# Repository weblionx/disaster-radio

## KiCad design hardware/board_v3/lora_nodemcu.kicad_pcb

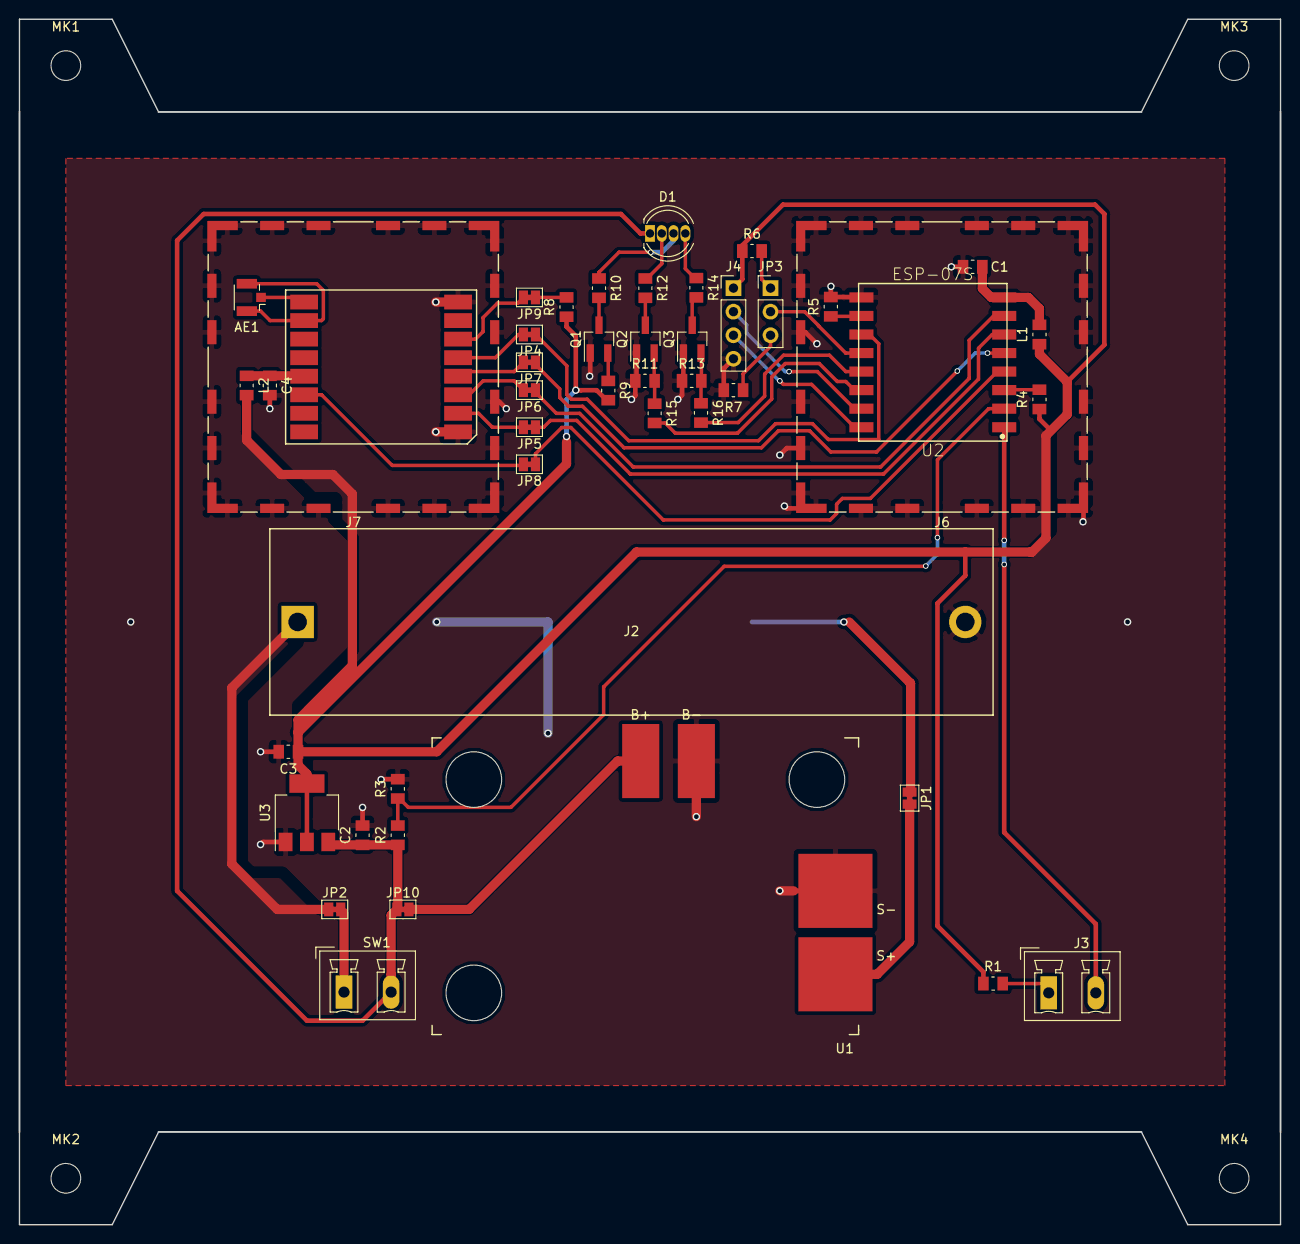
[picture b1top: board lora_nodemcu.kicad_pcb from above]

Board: 2 copper layers, 136.0 x 130.0 mm, 52 parts (1 on the bottom side), 45 nets.

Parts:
AE1: RFM95_Antenna; U.FL_Hirose_U.FL-R-SMT-1_Vertical
C1, C4: 0.1uF; C_0805_2012Metric_Pad1.15x1.50mm_HandSolder
C2, C3: 10uF; C_0805_2012Metric_Pad1.15x1.50mm_HandSolder
D1: LED_ARGB; LED_D5.0mm-4
J1: Solar Panel; solar_panel_conn
J2: LiPo 18650; BatteryHolder_MPD_BH-18650-PC2
J3: RESET_BUTTON; PhoenixContact_MCV_1,5_2-G-5.08_1x02_P5.08mm_Vertical
J4: ESP_PRGM; PinHeader_1x04_P2.54mm_Vertical
J6: RF_Shield_ESP-07S; Wuerth_36103305_30x30mm
J7: RF_Shield_RFM95; Wuerth_36103305_30x30mm
JP1: SOLAR_TP; SolderJumper-2_P1.3mm_Bridged_Pad1.0x1.5mm
JP2: LiPo_TP; SolderJumper-2_P1.3mm_Bridged_Pad1.0x1.5mm
JP3: PRGM_SELECT; PinHeader_1x03_P2.54mm_Vertical
JP4: CS; SolderJumper-2_P1.3mm_Bridged_Pad1.0x1.5mm
JP5: MISO; SolderJumper-2_P1.3mm_Bridged_Pad1.0x1.5mm
JP6: MOSI; SolderJumper-2_P1.3mm_Bridged_Pad1.0x1.5mm
JP7: CLK; SolderJumper-2_P1.3mm_Bridged_Pad1.0x1.5mm
JP8: D1; SolderJumper-2_P1.3mm_Bridged_Pad1.0x1.5mm
JP9: RST; SolderJumper-2_P1.3mm_Bridged_Pad1.0x1.5mm
JP10: MPPT_TP; SolderJumper-2_P1.3mm_Bridged_Pad1.0x1.5mm
L1, L2: JUMPER; L_0805_2012Metric_Pad1.15x1.50mm_HandSolder
MK1, MK2, MK3, MK4: Mounting_Hole; MountingHole_3.2mm_M3
Q1, Q2, Q3: 2N3904; SOT-23_Handsoldering
R1, R3, R4, R5, R6, R7, R8, R9, R11, R13, R15, R16: 10K; R_0805_2012Metric_Pad1.15x1.50mm_HandSolder
R2: 47K; R_0805_2012Metric_Pad1.15x1.50mm_HandSolder
R10: 1K; R_0805_2012Metric_Pad1.15x1.50mm_HandSolder
R12: 470; R_0805_2012Metric_Pad1.15x1.50mm_HandSolder
R14: 330; R_0805_2012Metric_Pad1.15x1.50mm_HandSolder
SW1: SW_SPST; PhoenixContact_MCV_1,5_2-G-5.08_1x02_P5.08mm_Vertical
U1: CN3791_module
U2: ESP-07S
U3: LM1117-3.3; SOT-223-3_TabPin2
U4: RFM95

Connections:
+3V3: C3.1, J4.1, L1.1, L2.2, R1.1, R4.1, R6.1, R8.1, R9.2, U3.2
+BATT: C2.1, D1.1, JP10.1, R2.1, SW1.2, U3.3
/3V3_ESP: C1.1, L1.2, U2.8
/3V3_RFM: C4.1, L2.1, U4.13
/BATT_TP: JP10.2, U1.3
/BLUE: D1.4, R14.1
/GREEN: D1.3, R10.1
/LIPO_CONN: J2.1, JP2.1
/LIPO_TP: JP2.2, SW1.1
/RED: D1.2, R12.1
/SOLAR_CONN: J1.2, JP1.1
/SOLAR_TP: JP1.2, U1.1
/SPI_CLK: JP7.1, U2.5
/SPI_MISO: JP5.1, U2.6
/SPI_MOSI: JP6.1, U2.7
GND: C1.2, C2.2, C3.2, C4.2, J1.1, J2.2, J4.4, J6.1, J7.1, Q1.1, Q2.1, Q3.1, R3.2, R5.2, R7.2, R11.1, R13.1, U1.2, U1.4, U2.9, U3.1, U4.1, U4.8
unnamed: AE1.1, U4.9
unnamed: AE1.2, U4.10
unnamed: J3.1, R1.2
unnamed: J3.2, U2.1
unnamed: J4.2, U2.15
unnamed: J4.3, U2.16
unnamed: JP3.1, R6.2
unnamed: JP3.2, U2.12
unnamed: JP3.3, R7.1
unnamed: JP4.1, U2.11
unnamed: JP4.2, U4.5
unnamed: JP5.2, U4.2
unnamed: JP6.2, U4.3
unnamed: JP7.2, U4.4
unnamed: JP8.1, U2.4
unnamed: JP8.2, U4.14
unnamed: JP9.1, R8.2
unnamed: JP9.2, U4.6
unnamed: Q1.2, R9.1
unnamed: Q1.3, R10.2
unnamed: Q2.2, R11.2, R15.1
unnamed: Q2.3, R12.2
unnamed: Q3.2, R13.2, R16.1
unnamed: Q3.3, R14.2
unnamed: R2.2, R3.1, U2.2
unnamed: R4.2, U2.3
unnamed: R5.1, U2.10
unnamed: R15.2, U2.14
unnamed: R16.2, U2.13

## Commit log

2018-08-09 barely working routing table
2018-08-20 Reduced size of slots in ground plane, increased width of power traces.
